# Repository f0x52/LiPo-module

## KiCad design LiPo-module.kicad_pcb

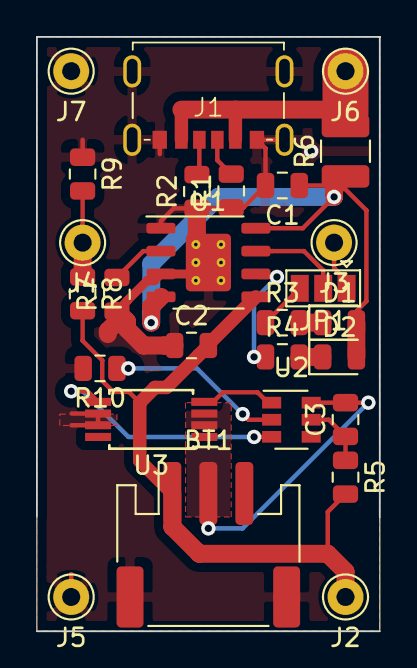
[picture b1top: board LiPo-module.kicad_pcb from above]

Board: 2 copper layers, 19.0 x 33.0 mm, 27 parts (0 on the bottom side), 19 nets.

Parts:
BT1: Battery; JST_PH_S3B-PH-SM4-TB_1x03-1MP_P2.00mm_Horizontal
C1, C2: 10uF; C_0805_2012Metric
C3: 0.1uF; C_0805_2012Metric
D1, D2: LED; LED_0805_2012Metric
J1: USB-C_Power
J2, J3, J4, J5, J6, J7: Conn_01x01_Male; Pin_D1.0mm_L10.0mm
JP1: SolderJumper_3_Open; SolderJumper-3_P1.3mm_Open_Pad1.0x1.5mm
R1, R2: 5.1K; R_0805_2012Metric
R3, R4: 1K; R_0805_2012Metric
R5: 470; R_0805_2012Metric
R6: 0.4; R_1210_3225Metric
R7: 2.2K; R_0805_2012Metric
R8: 10K; R_0805_2012Metric
R9: 33K; R_0805_2012Metric
R10: 2K; R_0805_2012Metric
U1: TP4056; SOIC-8-1EP_3.9x4.9mm_P1.27mm_EP2.514x3.2mm_ThermalVias
U2: DW01A; SOT-23-6
U3: FS8205A; TSSOP-8_4.4x3mm_P0.65mm

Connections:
+5V: J1.2, J1.5, J6.1, R6.2
/BATTERY: J4.1, R8.1, R9.2
/BAT_GND: BT1.2, C3.2, U2.6, U3.2, U3.3
/CHARGING: J3.1, JP1.1
/CS: R10.1, U2.2
/OC: U2.3, U3.5
/OD: U2.1, U3.4
/vBAT: BT1.1, C2.2, J2.1, R5.2, R8.2, U1.5
/vcc: C3.1, R5.1, U2.5
GND: BT1.MP, C1.2, C2.1, J1.1, J1.6, J5.1, J7.1, R1.1, R2.1, R7.1, R9.1, R10.2, U1.1, U1.3, U1.9, U3.6, U3.7
unnamed: C1.1, D1.2, D2.2, R6.1, U1.4, U1.8
unnamed: D1.1, R3.2
unnamed: D2.1, R4.2
unnamed: J1.3, R1.2
unnamed: J1.4, R2.2
unnamed: JP1.2, U1.7
unnamed: JP1.3, R3.1
unnamed: R4.1, U1.6
unnamed: R7.2, U1.2

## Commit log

2019-11-04 pcb design done
2019-11-04 pdf outputs
2019-11-04 connect ground island
2019-11-04 add lipo protection to schematic
2019-11-05 add lipo protection circuitry
2019-11-05 LICENSE GPL-3.0
